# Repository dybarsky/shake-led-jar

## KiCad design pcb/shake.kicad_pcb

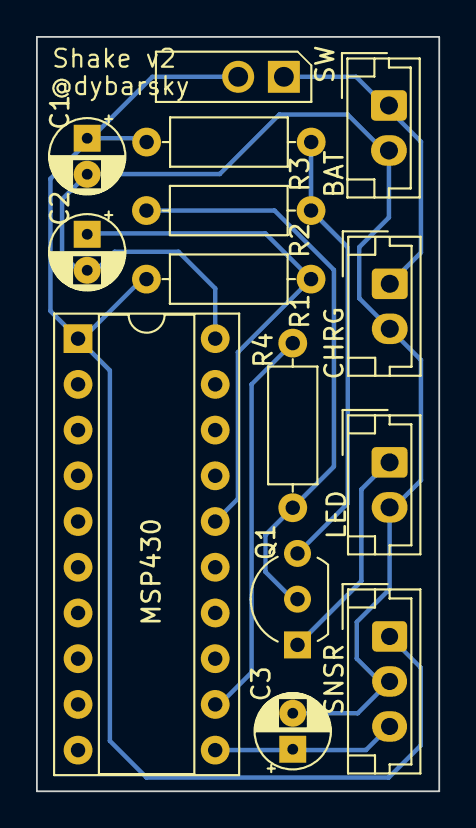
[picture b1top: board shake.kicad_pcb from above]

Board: 2 copper layers, 22.4 x 41.9 mm, 14 parts (0 on the bottom side), 8 nets.

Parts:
BAT: JST_EH_B2B-EH-A_1x02_P2.50mm_Vertical
C1, C2, C3: CP_Radial_D4.0mm_P2.00mm
CHRG: JST_EH_B2B-EH-A_1x02_P2.50mm_Vertical
LED: JST_EH_B2B-EH-A_1x02_P2.50mm_Vertical
MSP430: DIP-20_W7.62mm_Socket
Q1: TO-92L_Inline_Wide
R1, R2, R3, R4: R_Axial_DIN0207_L6.3mm_D2.5mm_P10.16mm_Horizontal
SNSR: JST_EH_B3B-EH-A_1x03_P2.50mm_Vertical
SW: TerminalBlock_TE_282834-2_1x02_P2.54mm_Horizontal

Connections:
+3.7V: BAT.1, C1.1, CHRG.1, MSP430.1, R1.1, R3.1, SNSR.1, SW.1, SW.2
GND: BAT.2, C1.2, C2.2, C3.2, CHRG.2, LED.2, MSP430.20, SNSR.2
LedVcc: LED.1, Q1.1
T1VCC: Q1.3, R2.1, R3.2
T1base: Q1.2, R2.2, R4.2
led: MSP430.12, R4.1
reset: C2.1, MSP430.16, R1.2
sensor: C3.1, MSP430.11, SNSR.3

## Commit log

2025-01-21 Implement led control
2025-01-21 Implement sensor routine
2025-01-21 Implement timer operations
2025-01-21 main.c
2025-01-21 Add Makefile
2025-01-21 Add gitignore
2025-01-21 Move c code to firmware folder
2025-01-21 Remove spaces
2025-01-24 Add PCB and Schematic kicad project
2025-01-24 Update kicad project
2025-01-24 Add gbr files
2025-01-24 Change sensor and led pins
2025-01-24 Update gitignore
2025-01-24 Add pcb and schematics media files
2025-01-24 Update kicad
2025-01-24 Add MIT licence
2025-02-10 Updated media files
2025-02-10 Update pcb and schematics
2025-02-12 Update pcb
2025-02-24 Updated gitignore
2025-02-24 Add Dockerifle
2025-02-24 Add github actions
2025-02-24 Add ifdef to headers
